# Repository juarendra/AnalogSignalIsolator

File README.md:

# Analog Signal Isolator

> Isolator sinyal analog 0–5 V untuk menghubungkan sensor ke ESP32, Arduino, MCU, atau PLC tanpa menyatukan ground kedua sisi.

> [!NOTE]
> Panduan pembeli pada halaman ini berlaku untuk PCB yang silkscreen-nya bertuliskan **`AIN`**, **`AOUT`**, `MCU SIDE`, `SENSOR SIDE`, dan `FIT ONE ONLY`.

> [!TIP]
> Produk dikirim sebagai **satu PCB yang sudah dirakit**. Mode bawaan untuk ESP32, yaitu `M2.4V1`, sudah terpasang. Paket tidak mencakup sensor, kabel, catu daya, maupun board ESP32.

<p align="center">
  <a href="DOC/USER_GUIDE/start-here.html"><strong>Mulai pemasangan PCB AIN/AOUT &rarr;</strong></a>
  &nbsp;·&nbsp;
  <a href="DOC/USER_GUIDE/assets/pinout-pcb-infographic.png"><strong>Unduh gambar pinout &rarr;</strong></a>
</p>

## Produk ini untuk apa?

Analog Signal Isolator adalah **jembatan aman untuk sinyal analog 0–5 V**. Modul ini menerima tegangan dari sensor di satu sisi, lalu mengirimkan kembali nilai yang sama secara analog ke ADC mikrokontroler/PLC di sisi lain—tanpa hubungan listrik langsung antara kedua ground.

Masalah yang diselesaikan modul ini adalah *ground loop*, noise, dan gangguan ketika sensor berada di mesin/panel yang berbeda dengan ESP32, Arduino, PLC, data logger, atau komputer yang terhubung USB. Sensor tetap memperoleh catu 5 V dari sisi terisolasi, sedangkan MCU membaca sinyal melalui `AOUT`.

```text
Sensor 0–5 V       Isolator analog optik              Mikrokontroler / PLC

AIN ─────────────▶ [ SENSOR SIDE  ║  MCU SIDE ] ─────────────▶ AOUT → ADC
GND sensor         ground terpisah / tidak tersambung          GND MCU
```

**Intinya:** jika sensor menunjukkan 2,50 V pada `AIN`, modul meneruskan nilai proporsional pada `AOUT` sesuai mode yang dipilih. Perangkat lunak kemudian mengubah pembacaan ADC tersebut kembali menjadi nilai sensor melalui kalibrasi dua titik.

## Contoh aplikasi

| Aplikasi | Cara modul digunakan | Manfaat |
| --- | --- | --- |
| **Data logger ESP32** | Sensor tekanan, level, atau posisi 0–5 V dipasang di sisi sensor; `AOUT` dibaca ESP32 pada sisi MCU. | Mengurangi noise dan risiko gangguan ground saat ESP32 memakai USB/Wi-Fi. |
| **Monitoring panel mesin** | Sensor analog pada panel mesin dihubungkan ke `AIN`; sistem monitoring terpisah membaca `AOUT`. | Ground sistem monitoring tidak perlu disatukan dengan ground panel. |
| **Input analog PLC** | Sinyal sensor 0–5 V diteruskan ke input analog PLC melalui sisi MCU. | Membantu pemisahan domain sensor dan kontrol. |
| **Gateway IoT retrofit** | Tambahkan ESP32/Arduino untuk membaca keluaran sensor pada alat lama tanpa mengubah wiring sensor utama. | Integrasi monitoring jarak jauh lebih aman dan rapi. |

> Modul ini bekerja untuk **tegangan analog DC 0–5 V yang sudah dikondisikan**. Untuk sensor 4–20 mA, RTD, thermocouple, AC, atau tegangan PLN, gunakan rangkaian pengondisi sinyal yang tepat terlebih dahulu.

## Kenapa menggunakan modul ini?

- **Isolasi galvanik** antara sisi sensor dan sisi MCU/PLC untuk membantu mengurangi *ground loop* dan gangguan.
- **Input sensor 0–5 V DC** dengan keluaran analog terisolasi `AOUT`.
- **Catu sensor 5 V terisolasi** tersedia langsung pada konektor sisi sensor, hingga **150 mA kontinu** untuk beban sensor.
- **Mode ESP32 2,4 V** sudah dipilih dari pabrik (`M2.4V1`); pilihan lain hanya untuk perubahan konfigurasi terkontrol.
- **Siap untuk dokumentasi dan produksi:** proyek KiCad, Gerber, BOM, skematik, serta prosedur pengujian tersedia di repositori.

## Gambaran koneksi

| MCU SIDE | SENSOR SIDE |
| --- | --- |
| `5V` — catu masuk modul | `5V` — catu keluar terisolasi untuk sensor (maks. 150 mA kontinu) |
| `GND` — ground MCU/PLC | `GND` — ground sensor terisolasi |
| `AOUT` — ke input ADC | `AIN` — dari output sensor 0–5 V |

> [!CAUTION]
> **Jangan hubungkan ground MCU ke ground sensor.** Kedua sisi harus tetap terpisah agar isolasi bekerja.

## Mulai cepat

1. Buka [Mulai di Sini — PCB AIN/AOUT](DOC/USER_GUIDE/start-here.html).
2. Pastikan `M2.4V1` masih terpasang sebagai mode bawaan ESP32. Jangan mengubah jumper mode kecuali Anda memang mengganti jenis host.
3. Hubungkan sensor 0–5 V ke `AIN` dan `GND` pada **SENSOR SIDE**.
4. Hubungkan ADC ke `AOUT`, catu +5 V ke `5V`, dan ground host ke `GND` pada **MCU SIDE**.
5. Nyalakan catu 5 V yang teratur dan memiliki pembatas arus, kemudian kalibrasikan pembacaan 0 V dan 5 V.

## Batas catu untuk sensor

Konektor `5V` pada **SENSOR SIDE** adalah keluaran dari DC/DC isolasi, bukan catu 5 V berdaya besar.

- Gunakan beban sensor total **maksimum 150 mA secara kontinu** (gabungan arus sensor dan aksesori yang mengambil daya dari konektor ini).
- Rating modul DC/DC yang dipasang adalah 5 V / 200 mA, tetapi sebagian arus dipakai oleh rangkaian isolator dan perlu margin untuk suhu serta lonjakan awal. Karena itu **200 mA bukan batas beban sensor eksternal**.
- Bila sensor memiliki arus *inrush*, relay, pemanas, atau motor, gunakan catu sensor terisolasi eksternal yang sesuai. Jangan mengambil daya beban tersebut dari PCB ini.

## Proteksi sistem yang direkomendasikan

PCB ini tidak memasang TVS atau PPTC. Untuk instalasi panel/mesin, pasang proteksi **di luar PCB** pada sisi yang tepat:

1. Gunakan catu **5 V DC teratur**; jangan hubungkan sumber dengan tegangan lebih dari 5 V ke `5V` pada MCU SIDE.
2. Pada kabel `+5V` menuju MCU SIDE, pasang **sekering atau PPTC**. Tentukan nilai *hold/trip* dari arus sistem dan uji arus awal; sebagai titik awal desain, rentang 250–500 mA lazim untuk jalur modul ini, bukan nilai yang otomatis cocok untuk semua sistem.
3. Pasang **TVS unidirectional dengan tegangan kerja 5 V** antara `+5V` dan `GND` **setelah** sekering/PPTC. Pilih energi impuls dan tegangan jepit berdasarkan lingkungan serta kemampuan catu; TVS bukan pengganti sekering.
4. Untuk kabel sensor panjang atau berada di lingkungan berisiko gangguan, TVS 5 V tambahan boleh dipasang dekat konektor **SENSOR SIDE**, dari `5V` ke `GND` sensor saja. Gunakan pelindung sinyal yang dirancang untuk jenis sensor pada jalur `AIN`; jangan memasang komponen sembarang yang mengubah akurasi sinyal.
5. Bila ada shield kabel, terminasi ke chassis/earth di titik masuk panel sesuai praktik sistem. Jangan memakai shield atau perangkat ukur untuk menyatukan `GND` sensor dan `GND` MCU.

> [!WARNING]
> Jangan memasang TVS, jumper, kabel, atau ground melintasi celah/penghalang isolasi. Untuk petir atau surge energi tinggi, gunakan SPD pada pintu masuk sistem dan catu yang sesuai. PCB ini bukan penangkal petir maupun perangkat bersertifikasi keselamatan.

## Dokumentasi

| Dokumen | Kegunaan |
| --- | --- |
| [Mulai di Sini — PCB AIN/AOUT](DOC/USER_GUIDE/start-here.html) | Panduan utama pembeli: jumper, wiring ESP32, uji pertama, dan troubleshooting. |
| [Pinout visual](DOC/USER_GUIDE/pinout-pcb.html) | Cara pemasangan dari foto PCB atas/bawah; buka di browser. |
| [Gambar pinout siap dibagikan](DOC/USER_GUIDE/assets/pinout-pcb-infographic.png) | Infografik untuk pembeli, marketplace, atau teknisi lapangan. |
| [Panduan pengguna](DOC/USER_GUIDE/panduan-visual.html) | Penjelasan kerja, mode, wiring, kalibrasi, dan troubleshooting. |
| [Indeks dokumen teknis](DOC/README.md) | Skematik, BOM, aturan PCB, dan prosedur pengujian. |

## Struktur proyek

| Folder | Isi |
| --- | --- |
| `DOC/USER_GUIDE/` | Panduan pembeli, pinout, gambar produk, dan aset visual. |
| `DOC/` | Skematik, BOM, pengujian, serta referensi teknis Rev B2. |
| `PCB/AnalogIsolator/AnalogIsolator/` | Proyek KiCad, library lokal, Gerber, dan drill file produksi. |

> Rev B2 tidak memasang TVS dan sekering resettable (PPTC) pada papan. Untuk pemasangan yang andal, gunakan catu host 5 V yang teratur, dibatasi arus, dan perlindungan surge pada level sistem bila diperlukan.

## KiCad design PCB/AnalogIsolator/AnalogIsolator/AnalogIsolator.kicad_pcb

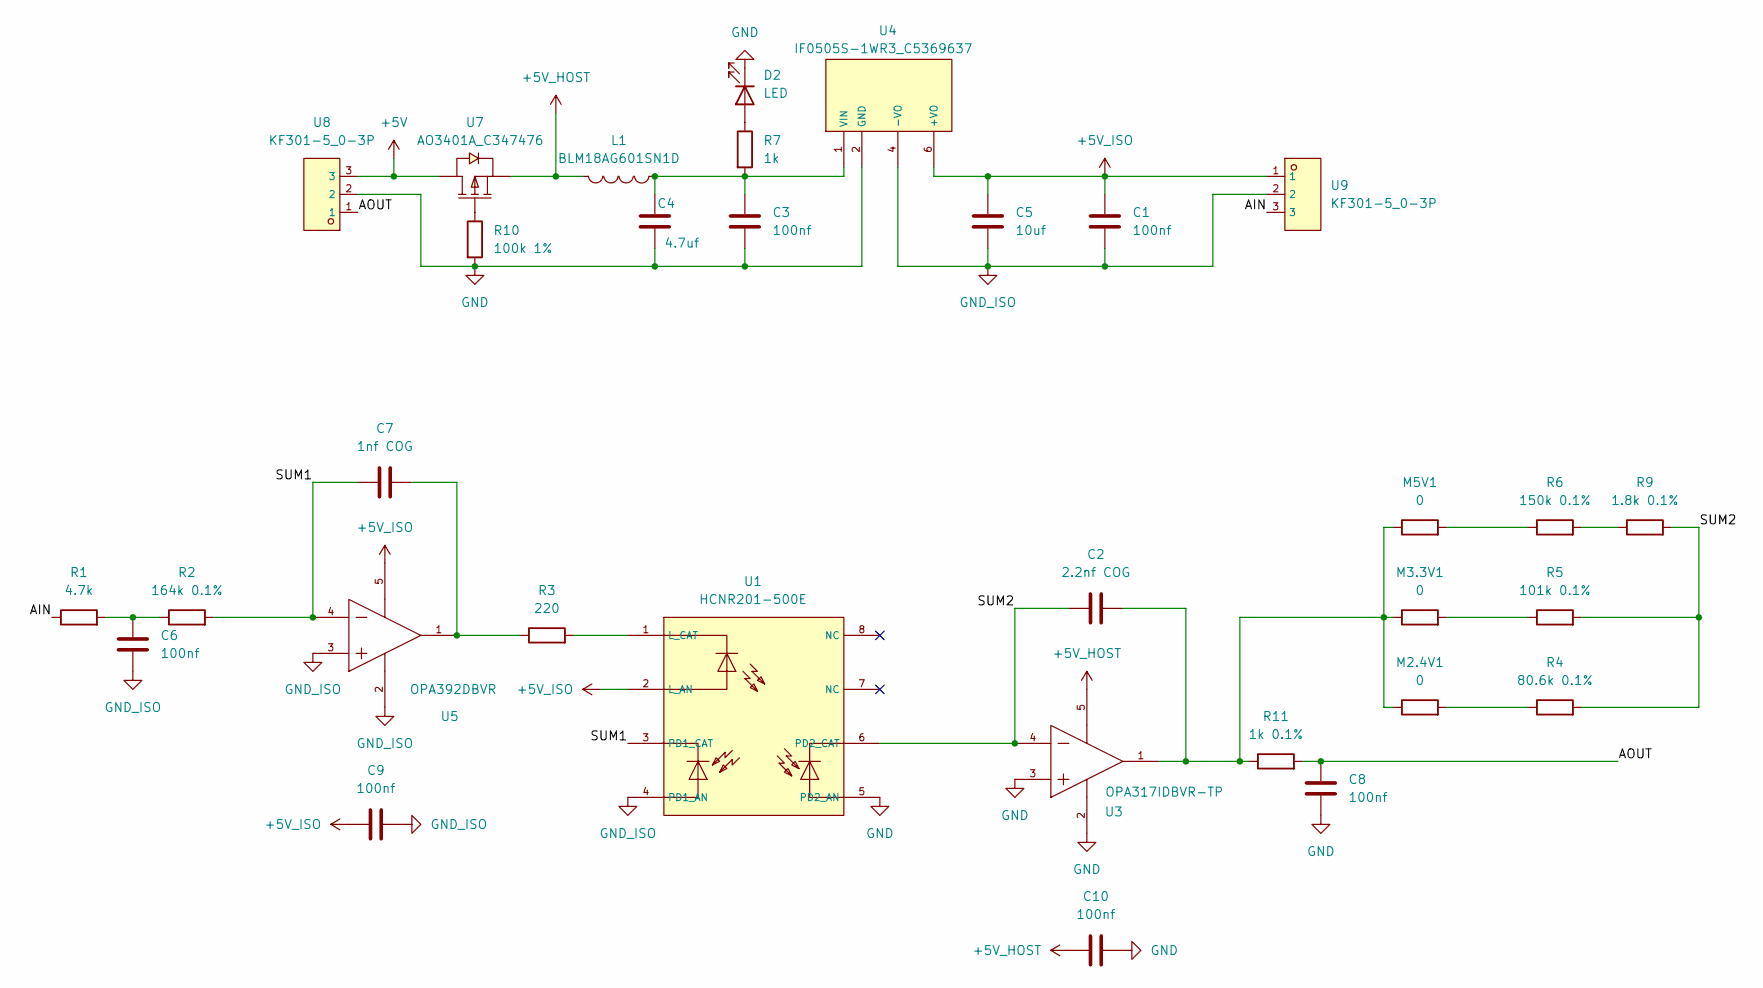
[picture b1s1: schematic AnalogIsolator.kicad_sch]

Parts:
C1, C3, C6, C8, C9, C10: 100nf; C_0603_1608Metric
C2: 2.2nf COG; C_0603_1608Metric
C4: 4.7uf; C_0603_1608Metric
C5: 10uf; C_0805_2012Metric
C7: 1nf COG; C_0603_1608Metric
D2: LED
L1: BLM18AG601SN1D; L0603; LCSC C19330
M2.4V1, M3.3V1, M5V1: 0; R_0603_1608Metric
R1: 4.7k; R_0603_1608Metric
R2: 164k 0.1%; R_0603_1608Metric
R3: 220; R_0603_1608Metric
R4: 80.6k 0.1%; R_0805_2012Metric
R5: 101k 0.1%; R_0805_2012Metric
R6: 150k 0.1%; R_0805_2012Metric
R7: 1k; R_0603_1608Metric
R9: 1.8k 0.1%; R_0805_2012Metric
R10: 100k 1%; R_0603_1608Metric
R11: 1k 0.1%; R_0603_1608Metric
U1: HCNR201-500E; OPTO-SMD-8P_L11.0-W9.0-P2.54-LS12.4-BL; LCSC C27465
U3: OPA317IDBVR-TP; SOT-23-5_L2.9-W1.6-P0.95-LS2.8-BR; LCSC C41431830
U4: IF0505S-1WR3_C5369637; PWRM-TH_BXXXXLS-1W; LCSC C5369637
U5: OPA392DBVR; SOT-23-5_L2.9-W1.6-P0.95-LS2.8-BL; LCSC C3647166
U7: AO3401A_C347476; SOT-23_L2.9-W1.3-P1.90-LS2.4-BR; LCSC C347476
U8, U9: KF301-5_0-3P; CONN-TH_3P-P5.00_KF301-5.0-3P; LCSC C474882

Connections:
+5V: U7.3 (D), U8.3
+5V_HOST: C10.1, L1.1, U3.5 (V+), U7.2 (S)
+5V_ISO: C1.1, C5.1, C9.1, U1.2 (L_AN), U4.6 (+VO), U5.5 (V+), U9.1
/AIN: R1.1, U9.3
/AOUT: C8.1, R11.2, U8.1
/SUM1: C7.1, R2.2, U1.3 (PD1_CAT), U5.4 (IN_-)
/SUM2: C2.1, R4.2, R5.2, R9.2, U1.6 (PD2_CAT), U3.4 (-IN)
GND: C3.2, C4.2, C8.2, C10.2, D2.1 (K), R10.2, U1.5 (PD2_AN), U3.2 (V-), U3.3 (+IN), U4.2 (GND), U8.2
GND_ISO: C1.2, C5.2, C6.2, C9.2, U1.4 (PD1_AN), U4.4 (-VO), U5.2 (V-), U5.3 (IN_+), U9.2
unnamed: C6.1, R1.2, R2.1
unnamed: D2.2 (A), R7.1
unnamed: M2.4V1.2, R4.1
unnamed: M3.3V1.2, R5.1
unnamed: M5V1.2, R6.1
unnamed: R6.2, R9.1
unnamed: R3.2, U1.1 (L_CAT)
unnamed: C2.2, M2.4V1.1, M3.3V1.1, M5V1.1, R11.1, U3.1 (OUT)
unnamed: C3.1, C4.1, L1.2, R7.2, U4.1 (VIN)
unnamed: C7.2, R3.1, U5.1 (OUT)
unnamed: R10.1, U7.1 (G)

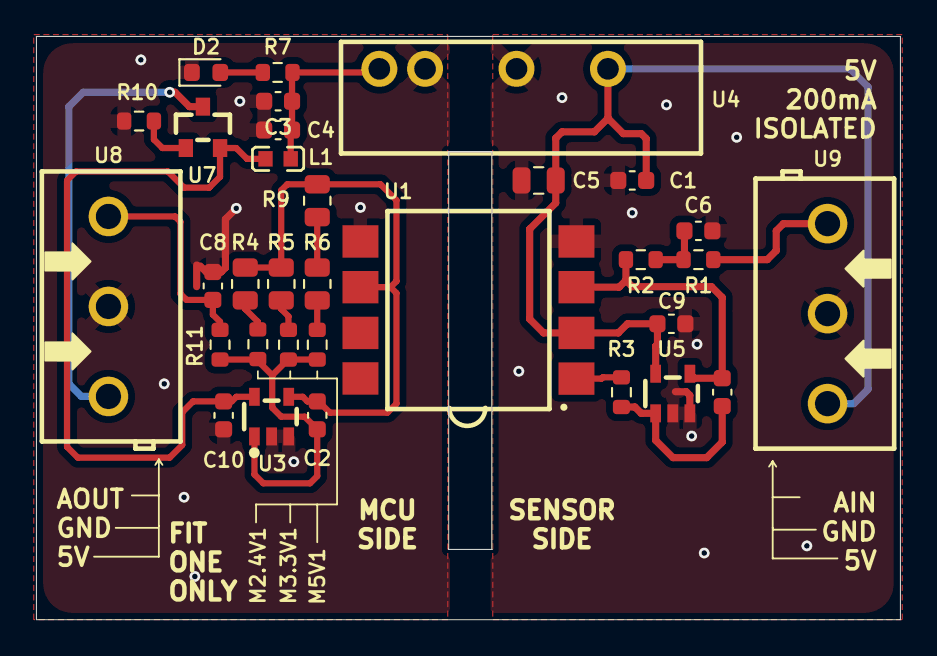
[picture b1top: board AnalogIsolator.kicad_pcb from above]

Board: 2 copper layers, 48.0 x 32.4 mm, 32 parts (0 on the bottom side), 20 nets.

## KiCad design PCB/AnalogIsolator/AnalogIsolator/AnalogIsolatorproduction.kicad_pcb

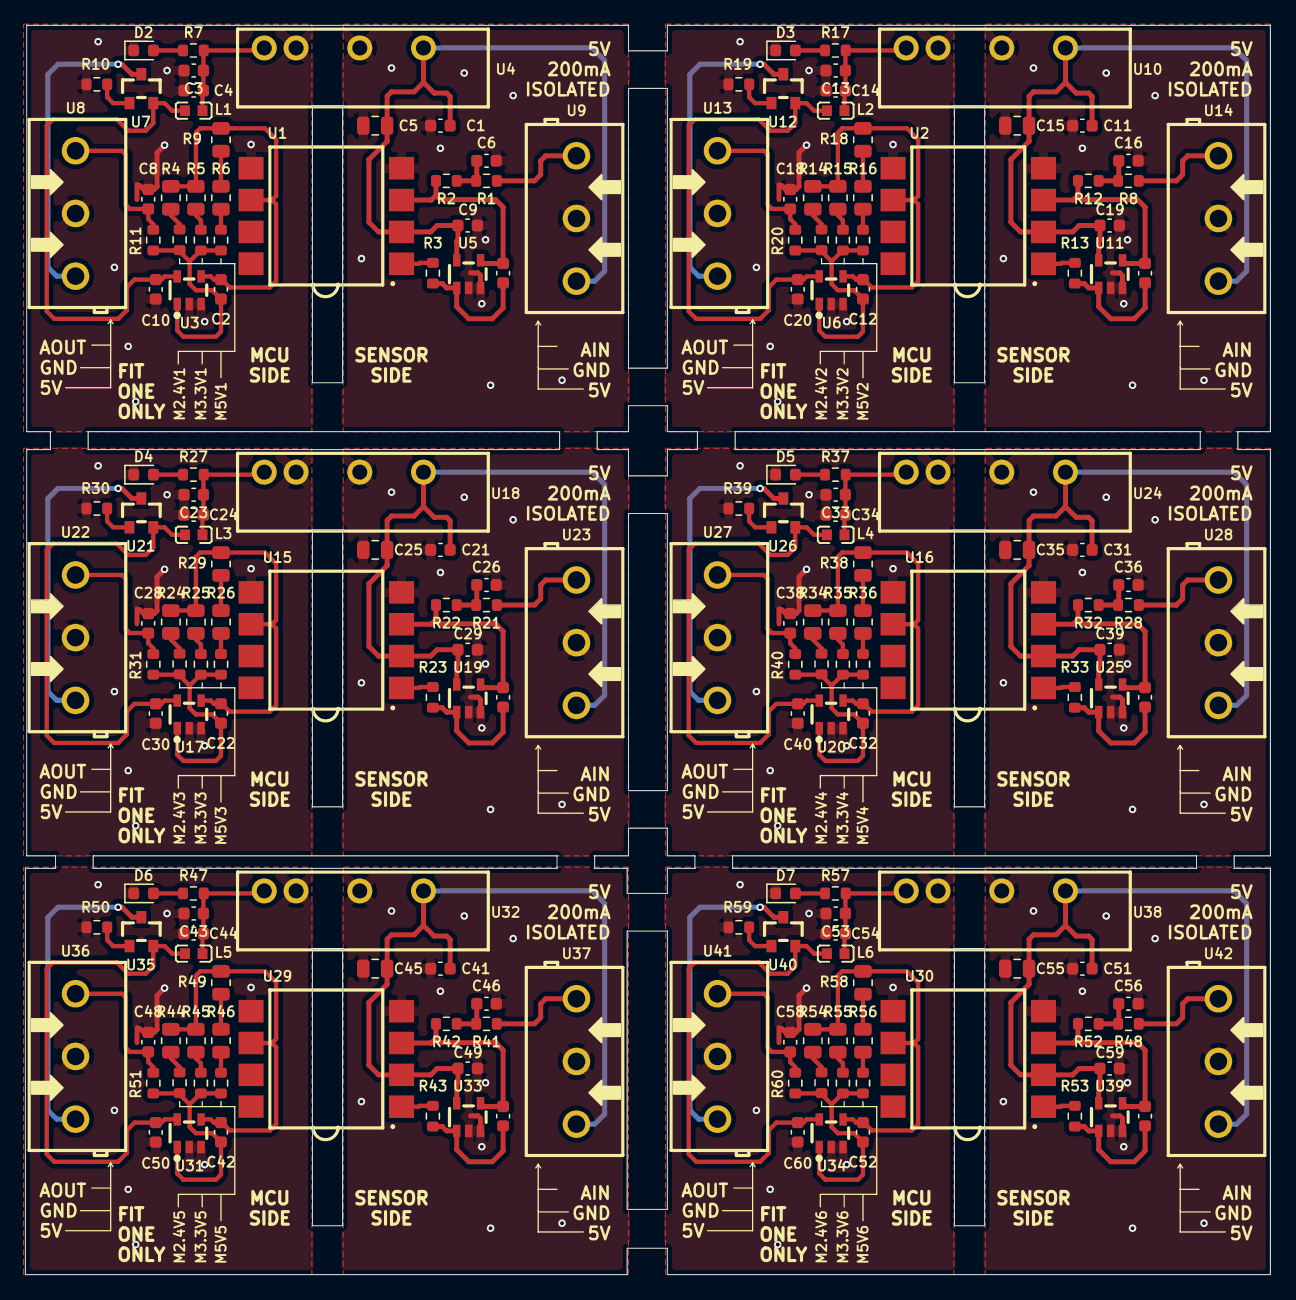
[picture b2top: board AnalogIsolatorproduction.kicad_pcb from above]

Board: 2 copper layers, 99.3 x 99.6 mm, 192 parts (0 on the bottom side), 20 nets.

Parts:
C1, C3, C6, C8, C9, C10, C11, C13, C16, C18, C19, C20, C21, C23, C26, C28, C29, C30, C31, C33, C36, C38, C39, C40, C41, C43, C46, C48, C49, C50, C51, C53, C56, C58, C59, C60: 100nf; C_0603_1608Metric
C2, C12, C22, C32, C42, C52: 2.2nf COG; C_0603_1608Metric
C4, C14, C24, C34, C44, C54: 4.7uf; C_0603_1608Metric
C5, C15, C25, C35, C45, C55: 10uf; C_0805_2012Metric
C7, C17, C27, C37, C47, C57: 1nf COG; C_0603_1608Metric
D2, D3, D4, D5, D6, D7: LED; LED_0603_1608Metric
L1, L2, L3, L4, L5, L6: BLM18AG601SN1D; L0603
M2.4V1, M2.4V2, M2.4V3, M2.4V4, M2.4V5, M2.4V6, M3.3V1, M3.3V2, M3.3V3, M3.3V4, M3.3V5, M3.3V6, M5V1, M5V2, M5V3, M5V4, M5V5, M5V6: 0; R_0603_1608Metric
R1, R8, R21, R28, R41, R48: 4.7k; R_0603_1608Metric
R2, R12, R22, R32, R42, R52: 164k 0.1%; R_0603_1608Metric
R3, R13, R23, R33, R43, R53: 220; R_0603_1608Metric
R4, R14, R24, R34, R44, R54: 80.6k 0.1%; R_0805_2012Metric
R5, R15, R25, R35, R45, R55: 101k 0.1%; R_0805_2012Metric
R6, R16, R26, R36, R46, R56: 150k 0.1%; R_0805_2012Metric
R7, R17, R27, R37, R47, R57: 1k; R_0603_1608Metric
R9, R18, R29, R38, R49, R58: 1.8k 0.1%; R_0805_2012Metric
R10, R19, R30, R39, R50, R59: 100k 1%; R_0603_1608Metric
R11, R20, R31, R40, R51, R60: 1k 0.1%; R_0603_1608Metric
U1, U2, U15, U16, U29, U30: HCNR201-500E; OPTO-SMD-8P_L11.0-W9.0-P2.54-LS12.4-BL
U3, U6, U17, U20, U31, U34: OPA317IDBVR-TP; SOT-23-5_L2.9-W1.6-P0.95-LS2.8-BR
U4, U10, U18, U24, U32, U38: IF0505S-1WR3_C5369637; PWRM-TH_BXXXXLS-1W
U5, U11, U19, U25, U33, U39: OPA392DBVR; SOT-23-5_L2.9-W1.6-P0.95-LS2.8-BL
U7, U12, U21, U26, U35, U40: AO3401A_C347476; SOT-23_L2.9-W1.3-P1.90-LS2.4-BR
U8, U9, U13, U14, U22, U23, U27, U28, U36, U37, U41, U42: KF301-5_0-3P; CONN-TH_3P-P5.00_KF301-5.0-3P

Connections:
+5V: U7.3 (D), U8.3, U12.3 (D), U13.3, U21.3 (D), U22.3, U26.3 (D), U27.3, U35.3 (D), U36.3, U40.3 (D), U41.3
+5V_HOST: C10.1, C20.1, C30.1, C40.1, C50.1, C60.1, L1.1, L2.1, L3.1, L4.1, L5.1, L6.1, U3.5 (V+), U6.5 (V+), U7.2 (S), U12.2 (S), U17.5 (V+), U20.5 (V+), U21.2 (S), U26.2 (S), U31.5 (V+), U34.5 (V+), U35.2 (S), U40.2 (S)
+5V_ISO: C1.1, C5.1, C9.1, C11.1, C15.1, C19.1, C21.1, C25.1, C29.1, C31.1, C35.1, C39.1, C41.1, C45.1, C49.1, C51.1, C55.1, C59.1, U1.2 (L_AN), U2.2 (L_AN), U4.6 (+VO), U5.5 (V+), U9.1, U10.6 (+VO), U11.5 (V+), U14.1, U15.2 (L_AN), U16.2 (L_AN), U18.6 (+VO), U19.5 (V+), U23.1, U24.6 (+VO), U25.5 (V+), U28.1, U29.2 (L_AN), U30.2 (L_AN), U32.6 (+VO), U33.5 (V+), U37.1, U38.6 (+VO), U39.5 (V+), U42.1
/AIN: R1.1, R8.1, R21.1, R28.1, R41.1, R48.1, U9.3, U14.3, U23.3, U28.3, U37.3, U42.3
/AOUT: C8.1, C18.1, C28.1, C38.1, C48.1, C58.1, R11.2, R20.2, R31.2, R40.2, R51.2, R60.2, U8.1, U13.1, U22.1, U27.1, U36.1, U41.1
/SUM1: C7.1, C17.1, C27.1, C37.1, C47.1, C57.1, R2.2, R12.2, R22.2, R32.2, R42.2, R52.2, U1.3 (PD1_CAT), U2.3 (PD1_CAT), U5.4 (IN_-), U11.4 (IN_-), U15.3 (PD1_CAT), U16.3 (PD1_CAT), U19.4 (IN_-), U25.4 (IN_-), U29.3 (PD1_CAT), U30.3 (PD1_CAT), U33.4 (IN_-), U39.4 (IN_-)
/SUM2: C2.1, C12.1, C22.1, C32.1, C42.1, C52.1, R4.2, R5.2, R9.2, R14.2, R15.2, R18.2, R24.2, R25.2, R29.2, R34.2, R35.2, R38.2, R44.2, R45.2, R49.2, R54.2, R55.2, R58.2, U1.6 (PD2_CAT), U2.6 (PD2_CAT), U3.4 (-IN), U6.4 (-IN), U15.6 (PD2_CAT), U16.6 (PD2_CAT), U17.4 (-IN), U20.4 (-IN), U29.6 (PD2_CAT), U30.6 (PD2_CAT), U31.4 (-IN), U34.4 (-IN)
GND: C3.2, C4.2, C8.2, C10.2, C13.2, C14.2, C18.2, C20.2, C23.2, C24.2, C28.2, C30.2, C33.2, C34.2, C38.2, C40.2, C43.2, C44.2, C48.2, C50.2, C53.2, C54.2, C58.2, C60.2, D2.1 (K), D3.1 (K), D4.1 (K), D5.1 (K), D6.1 (K), D7.1 (K), R10.2, R19.2, R30.2, R39.2, R50.2, R59.2, U1.5 (PD2_AN), U2.5 (PD2_AN), U3.2 (V-), U3.3 (+IN), U4.2 (GND), U6.2 (V-), U6.3 (+IN), U8.2, U10.2 (GND), U13.2, U15.5 (PD2_AN), U16.5 (PD2_AN), U17.2 (V-), U17.3 (+IN), U18.2 (GND), U20.2 (V-), U20.3 (+IN), U22.2, U24.2 (GND), U27.2, U29.5 (PD2_AN), U30.5 (PD2_AN), U31.2 (V-), U31.3 (+IN), U32.2 (GND), U34.2 (V-), U34.3 (+IN), U36.2, U38.2 (GND), U41.2
GND_ISO: C1.2, C5.2, C6.2, C9.2, C11.2, C15.2, C16.2, C19.2, C21.2, C25.2, C26.2, C29.2, C31.2, C35.2, C36.2, C39.2, C41.2, C45.2, C46.2, C49.2, C51.2, C55.2, C56.2, C59.2, U1.4 (PD1_AN), U2.4 (PD1_AN), U4.4 (-VO), U5.2 (V-), U5.3 (IN_+), U9.2, U10.4 (-VO), U11.2 (V-), U11.3 (IN_+), U14.2, U15.4 (PD1_AN), U16.4 (PD1_AN), U18.4 (-VO), U19.2 (V-), U19.3 (IN_+), U23.2, U24.4 (-VO), U25.2 (V-), U25.3 (IN_+), U28.2, U29.4 (PD1_AN), U30.4 (PD1_AN), U32.4 (-VO), U33.2 (V-), U33.3 (IN_+), U37.2, U38.4 (-VO), U39.2 (V-), U39.3 (IN_+), U42.2
unnamed: C6.1, C16.1, C26.1, C36.1, C46.1, C56.1, R1.2, R2.1, R8.2, R12.1, R21.2, R22.1, R28.2, R32.1, R41.2, R42.1, R48.2, R52.1
unnamed: D2.2 (A), D3.2 (A), D4.2 (A), D5.2 (A), D6.2 (A), D7.2 (A), R7.1, R17.1, R27.1, R37.1, R47.1, R57.1
unnamed: M2.4V1.2, M2.4V2.2, M2.4V3.2, M2.4V4.2, M2.4V5.2, M2.4V6.2, R4.1, R14.1, R24.1, R34.1, R44.1, R54.1
unnamed: M3.3V1.2, M3.3V2.2, M3.3V3.2, M3.3V4.2, M3.3V5.2, M3.3V6.2, R5.1, R15.1, R25.1, R35.1, R45.1, R55.1
unnamed: M5V1.2, M5V2.2, M5V3.2, M5V4.2, M5V5.2, M5V6.2, R6.1, R16.1, R26.1, R36.1, R46.1, R56.1
unnamed: R6.2, R9.1, R16.2, R18.1, R26.2, R29.1, R36.2, R38.1, R46.2, R49.1, R56.2, R58.1
unnamed: R3.2, R13.2, R23.2, R33.2, R43.2, R53.2, U1.1 (L_CAT), U2.1 (L_CAT), U15.1 (L_CAT), U16.1 (L_CAT), U29.1 (L_CAT), U30.1 (L_CAT)
unnamed: C2.2, C12.2, C22.2, C32.2, C42.2, C52.2, M2.4V1.1, M2.4V2.1, M2.4V3.1, M2.4V4.1, M2.4V5.1, M2.4V6.1, M3.3V1.1, M3.3V2.1, M3.3V3.1, M3.3V4.1, M3.3V5.1, M3.3V6.1, M5V1.1, M5V2.1, M5V3.1, M5V4.1, M5V5.1, M5V6.1, R11.1, R20.1, R31.1, R40.1, R51.1, R60.1, U3.1 (OUT), U6.1 (OUT), U17.1 (OUT), U20.1 (OUT), U31.1 (OUT), U34.1 (OUT)
unnamed: C3.1, C4.1, C13.1, C14.1, C23.1, C24.1, C33.1, C34.1, C43.1, C44.1, C53.1, C54.1, L1.2, L2.2, L3.2, L4.2, L5.2, L6.2, R7.2, R17.2, R27.2, R37.2, R47.2, R57.2, U4.1 (VIN), U10.1 (VIN), U18.1 (VIN), U24.1 (VIN), U32.1 (VIN), U38.1 (VIN)
unnamed: C7.2, C17.2, C27.2, C37.2, C47.2, C57.2, R3.1, R13.1, R23.1, R33.1, R43.1, R53.1, U5.1 (OUT), U11.1 (OUT), U19.1 (OUT), U25.1 (OUT), U33.1 (OUT), U39.1 (OUT)
unnamed: R10.1, R19.1, R30.1, R39.1, R50.1, R59.1, U7.1 (G), U12.1 (G), U21.1 (G), U26.1 (G), U35.1 (G), U40.1 (G)
